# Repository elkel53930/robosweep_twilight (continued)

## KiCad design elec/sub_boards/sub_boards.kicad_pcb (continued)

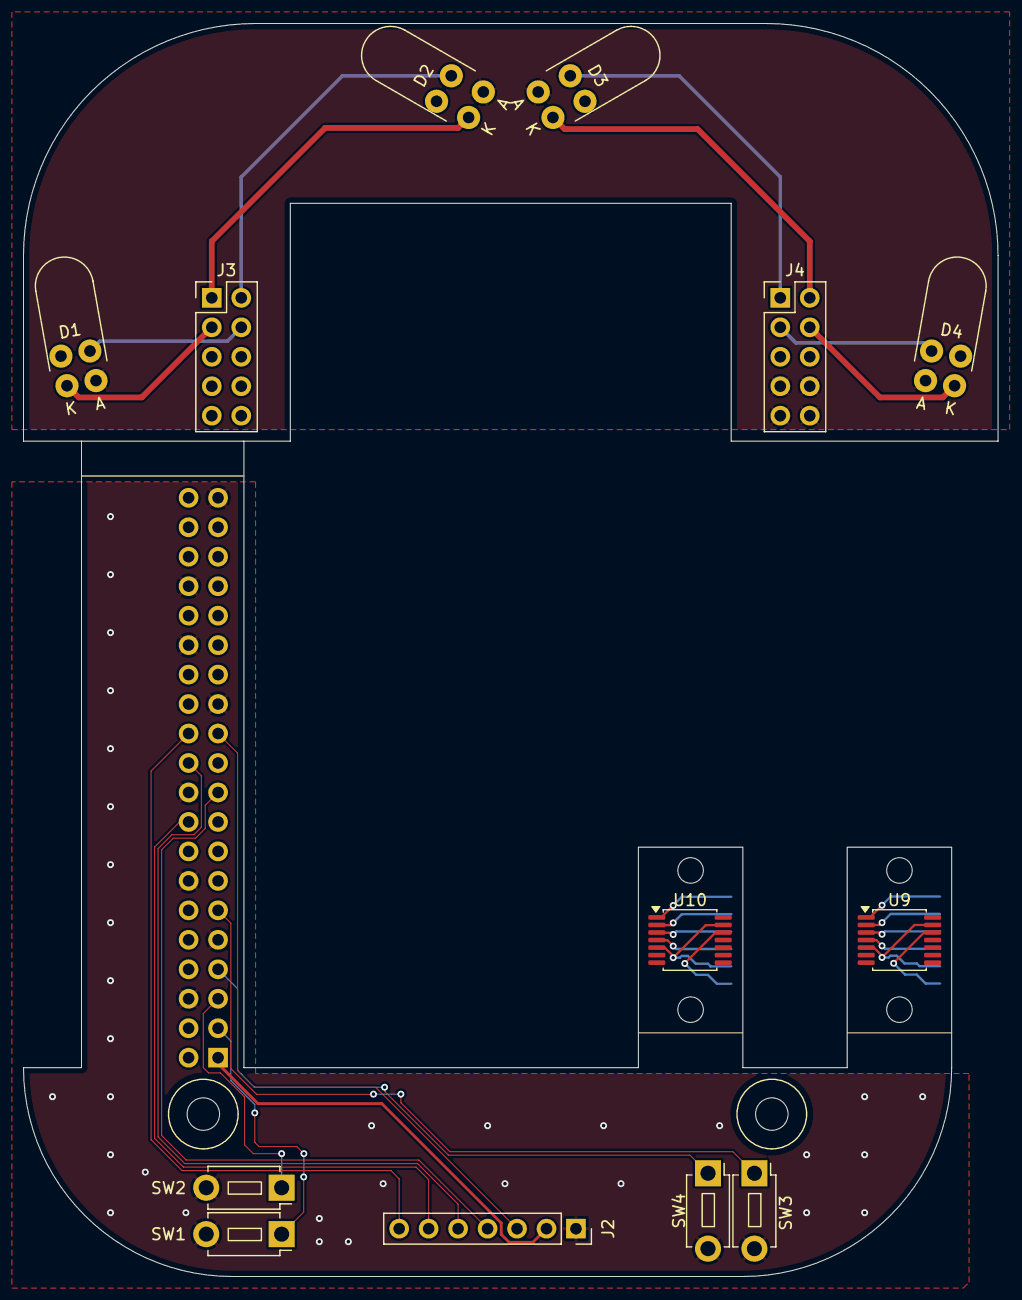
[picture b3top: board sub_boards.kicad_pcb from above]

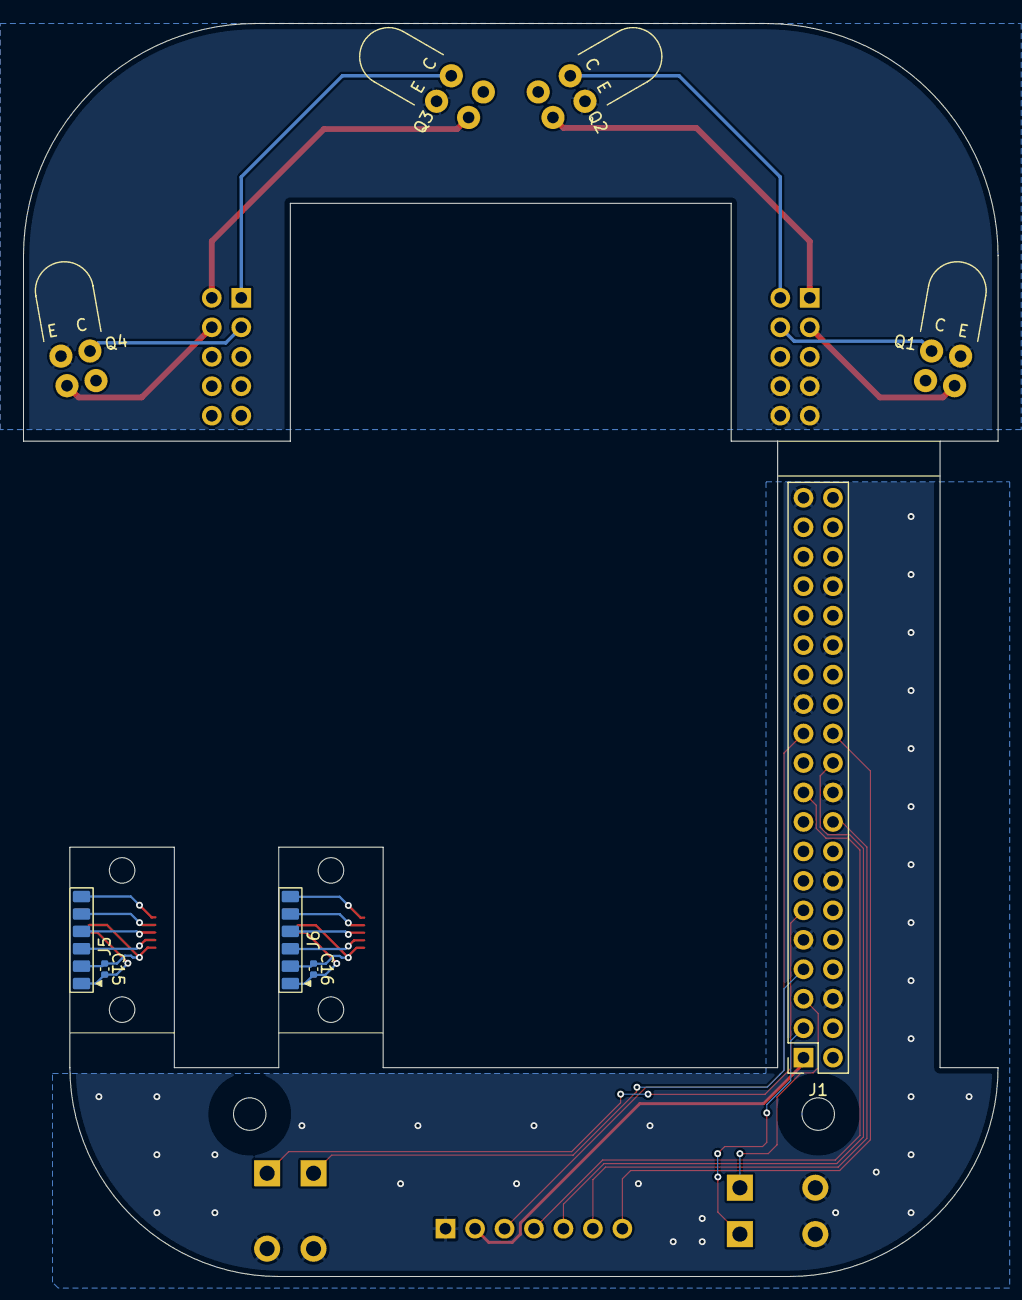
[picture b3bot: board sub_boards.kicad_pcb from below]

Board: 2 copper layers, 84.0 x 108.0 mm, 28 parts (9 on the bottom side), 33 nets.

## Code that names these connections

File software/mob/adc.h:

#ifndef ADC_H
#define ADC_H

#include <Arduino.h>
#include <SPI.h>

class ADC{
public:
	ADC(SPIClass& spi_bus);
	void batt_read(float &voltage);
	void lf_read(uint16_t &result);
	void ls_read(uint16_t &result);
	void rf_read(uint16_t &result);
	void rs_read(uint16_t &result);
private:
	// ピン定数
	static constexpr int PIN_MISO = 9;
	static constexpr int PIN_MOSI = 10;
	static constexpr int PIN_SCK  = 11;
	static constexpr int BATT_CS   = 1;
	static constexpr int LF_CS = 16;
	static constexpr int LS_CS = 15;
	static constexpr int RF_CS = 40;
	static constexpr int RS_CS = 41;
	
	SPIClass& spi;
};

#endif

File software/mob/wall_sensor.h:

#ifndef WALL_SENSOR_H
#define WALL_SENSOR_H

#include <Arduino.h>
#include "adc.h"

class WallSensor {
public:
	WallSensor(ADC& adc);
	uint16_t lf();
	uint16_t rf();
	uint16_t ls();
	uint16_t rs();
	
	// 壁センサ用LEDの有効/無効（消費電力対策）
	void set_enabled(bool enabled);
	bool is_enabled() const;
private:
	ADC& adc_;
	bool enabled_ = true;

	// 定数
	static constexpr uint16_t LF_EN = 6;
	static constexpr uint16_t LS_EN = 7;
	static constexpr uint16_t RF_EN = 2;
	static constexpr uint16_t RS_EN = 42;

	static constexpr uint32_t EN_DELAY_US = 100;
};

#endif

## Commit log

2025-10-08 Add schematics of main board
2025-10-11 アートワーク : 部品配置
2025-10-11 アートワーク : 部品配置完了
2025-10-11 Add .gitignore for KiCad
2025-10-11 アートワーク : 部品配置微修正
2025-10-11 アートワーク : 配線完了
2025-10-11 アートワーク : 微修正
2025-10-12 回路図 : 3.0Vから3.3Vに変更 アートワーク : コネクタピン配などのシルクを追加
2025-10-17 部品名を修正
2025-11-05 定数や型番の修正
2025-12-09 充電回路追加
2025-12-11 部品名追加
2025-12-12 アートワーク開始
2025-12-13 アートワークひととおり完成
2025-12-13 Sub boardsの回路図作成
2025-12-13 サブ基板アートワーク完了
2025-12-13 アートワーク微修正
2025-12-18 12/18 基板発注
2025-12-27 メイン基板を製造用に出図
2025-12-27 サブ基板を製造用に出図
2025-12-27 アーム基板WIP
2025-12-27 KiCadのプロジェクトファイルをelecディレクトリ以下に移動
2025-12-27 アームのテストプログラム
2025-12-27 スピード指定付きの角度設定コマンド
2025-12-28 アーム基板テストコード(test.py)
2025-12-28 ファイル実行中は電流値をグラフ表示する
2025-12-28 電流値の送信間隔を25msに変更
2025-12-28 自動でボールキャッチを検知して投げるテスト(throw_test.py)
2025-12-28 README.mdを更新
2026-01-02 ARMのフォルダにアーム関連のコードを移動
2026-01-02 Mobile platform(ESP32)のプロジェクトを追加
2026-01-02 if_pyとcamera_pyを追加
2026-01-02 KiCad用.gitignoreを修正
2026-01-02 サブボード（IFボード）を修正
2026-01-03 imu.rsを移植
2026-01-03 IMUをクラス化
2026-01-03 バッテリ電圧取得の動作確認
2026-01-05 アームボードのモータードライバを変更
2026-01-05 抵抗などの型番を指定
2026-01-09 ARMボード発注
2026-01-12 Mobのファームウェアを追加
    - IMU
    - LED
    - Motor
    - Wall sensors
2026-01-12 Add encoder support to the mob software
2026-01-12 Mobボードの動作確認完了
2026-01-17 アーム基盤の動作確認
2026-01-17 カメラによるボール検出
2026-01-17 アームボードの動作確認
2026-01-17 センサをまとめて扱うsensorsクラスを追加
2026-01-17 main menu
2026-01-18 RS204MDをUARTで操作するコード
2026-01-19 ARMボードから不要な回路を削除
2026-01-24 オドメトリ追加、PC側のアプリ追加
2026-01-24 起動時の壁センサをオフに
2026-01-24 フタバのデジタルサーボを制御するコード
2026-01-24 ホイールベースの値を修正
2026-01-24 旋回コマンド追加
2026-01-25 足立法のPythonによる実装
2026-01-25 テストスクリプト改良
2026-01-25 テスト用の迷路データを追加
2026-01-26 SENを定期的に送るのではなく、PCからの要求に応じて送るように変更
2026-01-26 pc_comm.pyが起動時に壁センサをオンにし、終了時オフにするように変更
2026-01-26 回路図更新
    ・壁センサLEDの抵抗値を100Ωに変更
    ・電源スイッチを削除
    ・ESP32のENにプルアップ追加
2026-01-27 FWDコマンドの距離累積バグ修正と信頼性向上
    主要な修正:
    - FWDコマンドの距離計算を修正（fwd_goal_dist_mmを+=から=に変更）
    複数のFWDコマンド間で目標距離が累積される問題を解決
    - RDSTとRANGコマンドにDONE応答を追加し、同期を確実に
    - FWDコマンド実行中の赤色LED表示を追加（実行中点灯、完了時消灯）
    - latency timerを設定するシェルスクリプトを追加
2026-01-27 ESP32のリセットスクリプトを修正
2026-01-27 FWDテストスクリプトとIMU設定を改善、ジャイロキャリブレーション機能を追加
    - fwd.py: FWD/STOPコマンドの速度・加速度パラメータを定数化し調整しやすく
    - fwd.py: GCALコマンドを追加してテスト開始前にジャイロキャリブレーションを実行
    - fwd.py: 入力バッファをクリアしてDONE応答の信頼性を向上
    - fwd.py: テストシーケンスを拡張（追加のRDST/RANG/FWD/STOPコマンド）
    - imu.cpp: ODRを6.66kHzから416Hzに変更してノイズを低減
    - imu.cpp: ジャイロ/加速度センサの設定を改善（自動インクリメント、ハイパフォーマンスモード）
2026-01-27 IMUのジャイロ設定を±1000dpsに変更し、STOPコマンドの速度下限を20mm/sに設定
    - imu.cpp/.h: ジャイロスコープのフルスケールを±2000dpsから±1000dpsに変更
    - 感度が35 mdps/LSBに向上（分解能2倍）
    - マイクロマウスの旋回速度には±1000dpsで十分
    - mob.ino: STOPコマンドの最低速度を20mm/sに設定
    - 減速ロジックは維持しつつ、速度が20mm/s未満にならないよう制限
    - 目標距離到達時のみ停止してDONEを返す
2026-01-27 壁センサーの差分計算で負の値を防ぐ
    - wall_sensor.cpp: LEDオフ時の値がオン時より大きい場合は0を返すように修正
    - lf(), rf(), ls(), rs()の4つの関数すべてで対応
    - uint16_tのアンダーフローを防止
2026-01-27 直進時の角度フィードバック追加
2026-01-27 fwd.py : マウスへコマンドを送るクラスを作成
2026-01-27 壁センサ（RS/LS）を用いた直進フィードバックをFWD/STOPに統合し、100未満は無効・両方有効時は平均、片側のみは片側のみの補正とするロジックを追加。中央基準値240に対する誤差から補正値を算出し、角度フィードバックと合算して直進安定性を向上。デバッグ出力で補正量の確認も可能にした。
2026-01-28 fwd.pyの制御クラスをMobileBaseに整理し、コマンド系メソッド名をcmd_*に統一。旋回角をπベースに変更し、右左/180度旋回や前後進などの高水準動作を追加。メインのテストシーケンスを簡潔化し、壁センサON/OFFやSEN取得の流れを整備。
2026-01-28 角速度フィードバック、STOP時のバックオフ
2026-01-28 低速連続動作コマンド(LFWD/LBACK/LTURNL/LTURNR/LSTOP)を実装
    - mob.ino: LatchMode状態機械を追加し、低速連続動作を実現
    - LFWD/LBACK: 50mm/sで連続前進/後退
    - LTURNL/LTURNR: 90deg/s相当で連続旋回
    - LSTOP: 低速動作の停止
    - 既存のFWD/STOP/TURNプロファイルとの競合を回避
    - fwd.py → mobile_base.pyに改名し、L*コマンドのメソッドを追加
2026-01-28 探索走行実装
2026-01-28 ゴール時の壁情報が迷路情報に反映されない問題を修正
2026-01-28 ゴールしたときの壁情報がはんえいされていないばぐをしゅうせい
2026-01-28 バグ修正
2026-01-29 アーム基板v2の回路図＆アートワーク
2026-01-31 アームボードのグリッド原点を変更
2026-02-01 QSTPコマンド
2026-02-01 ボールの角度の距離推定（間違ってるようだ）
2026-02-01 futaba_servo.pyで角度指定できるように。角度リミット追加。
2026-02-07 ボールのキャッチ・投擲テスト
2026-02-07 迷路探索でゴールにたどり着けない場合のエラー処理を追加
2026-02-07 スレッド分割した探索
2026-02-07 走行中のボール検出
2026-02-07 カメラのウォームアップ廃止
2026-02-07 アーム制御用のスクリプトをarm.pyに統合
2026-02-07 定数をArmクラスに移動
2026-02-07 QSTPの加速度を緩やかに変更
2026-02-07 Armをsolve_maze_threaded.pyに追加
2026-02-07 ゴール後、最後に訪れてから時間が経過しているマスめがけて探索を再開するように変更
2026-02-08 ArmDummy追加。カメラのデッドロック解消
2026-02-08 ボール誤検出対策
    彩度(S)下限を150に引き上げ
    明度(V)上限を200に引き下げ
2026-02-08 ボール検出結果の出力先を走行ごとに分割
2026-02-08 mobile_base_threadedにJOGFWD, JOGBACKコマンドを追加
2026-02-08 前進中にボールを検出して角度と位置を調整
2026-02-08 ボールに対する位置決めの改善
2026-02-11 ttyデバイスのデフォルト名を設定
2026-02-11 モータPWMのポートをD11からD5に変更
2026-02-11 ランチャーサーボの初期位置を180度に設定(バネ解放)
2026-02-11 探索してボールキャッチ
2026-02-11 途中でボールをキャッチしてゴールについたら投げる
2026-02-12 壁フィードバックを改善
    壁の誤差によって角度の目標値を直接変化させる。
    STOP時には壁センサ補正を行わないようにする。
2026-02-12 ボール検出キャリブレーション用GUIアプリを追加
    - manual_calibration.py: キャリブレーションデータ収集用GUI
    - リアルタイムカメラ表示、10回計測の中央値採用
    - 距離・角度の自動値更新で効率的なデータ収集
    - πラジアン単位での角度管理
    - アーム連携（起動時RUN_POSITION移動、終了時トルクオフ）
    - CALIBRATION_MANUAL.md: 詳細な操作マニュアル
2026-02-12 キャリブレーションデータ処理スクリプトを追加
    - generate_mirror_data.py: 左右対称データ生成スクリプト
    - 正の角度データから負の角度データを自動生成
    - カメラの左右対称性を仮定した補完
    - X座標の左右反転、角度の符号反転
    - 元データとマージして角度・距離でソート
    - データ統計情報の表示
2026-02-12 キャッチ時の位置補正を一回で住むように
2026-02-12 キャリブレーションシート生成スクリプト
2026-02-14 ボール検出時の減速度を緩和。ボールキャッチ後、センサーキャリブレーション実施
2026-02-14 メイン状態マシン実装
2026-02-14 マップ表示に歩数表示機能を追加。投擲位置の座標を修正。
2026-02-14 ボールを見失った場合に、早めに諦める
2026-02-14 Add debug tools and timestamped output
2026-02-14 Update ball handling logic
2026-02-14 バグ修正、
2026-02-18 ２号機への対応
2026-02-18 LANによる通信テスト (Client)
2026-02-18 LANによる通信テスト(server)
2026-02-19 Add compact and ultra-compact maze data formats
    - Add write_maze_compact/read_maze_compact for hex-based compression (47% size reduction)
    - Add write_maze_ultracompact/read_maze_ultracompact for binary+base64 compression (31% size reduction)
    - Add export_compact/import_compact methods to BaseExplorer class
    - Add export_ultracompact/import_ultracompact methods to BaseExplorer class
    - Add --compact-test option to test_step_solver.py for format validation
    - Add comprehensive Japanese documentation in COMPACT_FORMAT_DOC.md
2026-02-19 COMMの通信にノンブロッキング受信を追加
2026-02-19 Machine IDに応じてスタート位置や投擲位置を変更
2026-02-19 ゴール選択時の条件を追加
    ・到達不可能と判明していないこと
    ・少し離れていること
    ・自分の担当エリア内であること
2026-02-19 足立法に仮想壁機能を追加
    以下のようにして仮想壁を設定できる。Trueで仮想壁を設定、Falseで仮想壁を解除。
    explorer.set_virtual_wall(0,3, Direction.SOUTH, True)
    オールクリアもできる。
    explorer.clear_virtual_walls()
    仮想壁は歩数マップの計算において、実際の壁と同様に考慮される。
2026-02-20 サーバースクリプトを追加し、迷路情報を送信
    また、迷路情報をマージする機能を追加した。
2026-02-20 wait_detection_update()が呼び出し後の更新だけを検出するように修正
2026-02-20 マルチエージェント対応
2026-02-20 ボール検出が可能なエリアを制限
2026-02-20 衝突回避パラメータ調整
2026-02-20 スタートゲート対応
2026-02-20 ボール検出の条件を緩和
2026-02-20 スタートゲートに関する挙動をアームで知らせる
2026-02-21 大会直前の修正
2026-02-21 不要なファイルを削除
2026-02-21 コメント修正
2026-06-11 Add README.md
2026-06-11 Add block diagram
